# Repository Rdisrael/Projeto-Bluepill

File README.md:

# PCB SHIELD BLUEPILL

# Resumo
Projeto idealizado com o objetivo de auxiliar as aulas de microcontroladores do IFSP-GRU. Por meio da integração de diversos módulos, componentes e protocolos de comunicação em apenas uma placa de circuito impresso, será possível um aprendizado mais rápido e gradual para os alunos.

# Documentação
https://docs.google.com/spreadsheets/d/1qsbzq-tmwSNhySCmtm99sBOb9c8ssFgKAU8AfdciUCU/edit?usp=sharing

*Salve o projeto no disco local(C:) para que todos os componentes e modelos 3D sejam automaticante carregados*

# Autores

**Rogério Dantas**

https://www.linkedin.com/in/roger-dantas-b04025137/

**Israel R. Dutra**

www.linkedin.com/in/israel-rodrigues-dutra-6947281a0

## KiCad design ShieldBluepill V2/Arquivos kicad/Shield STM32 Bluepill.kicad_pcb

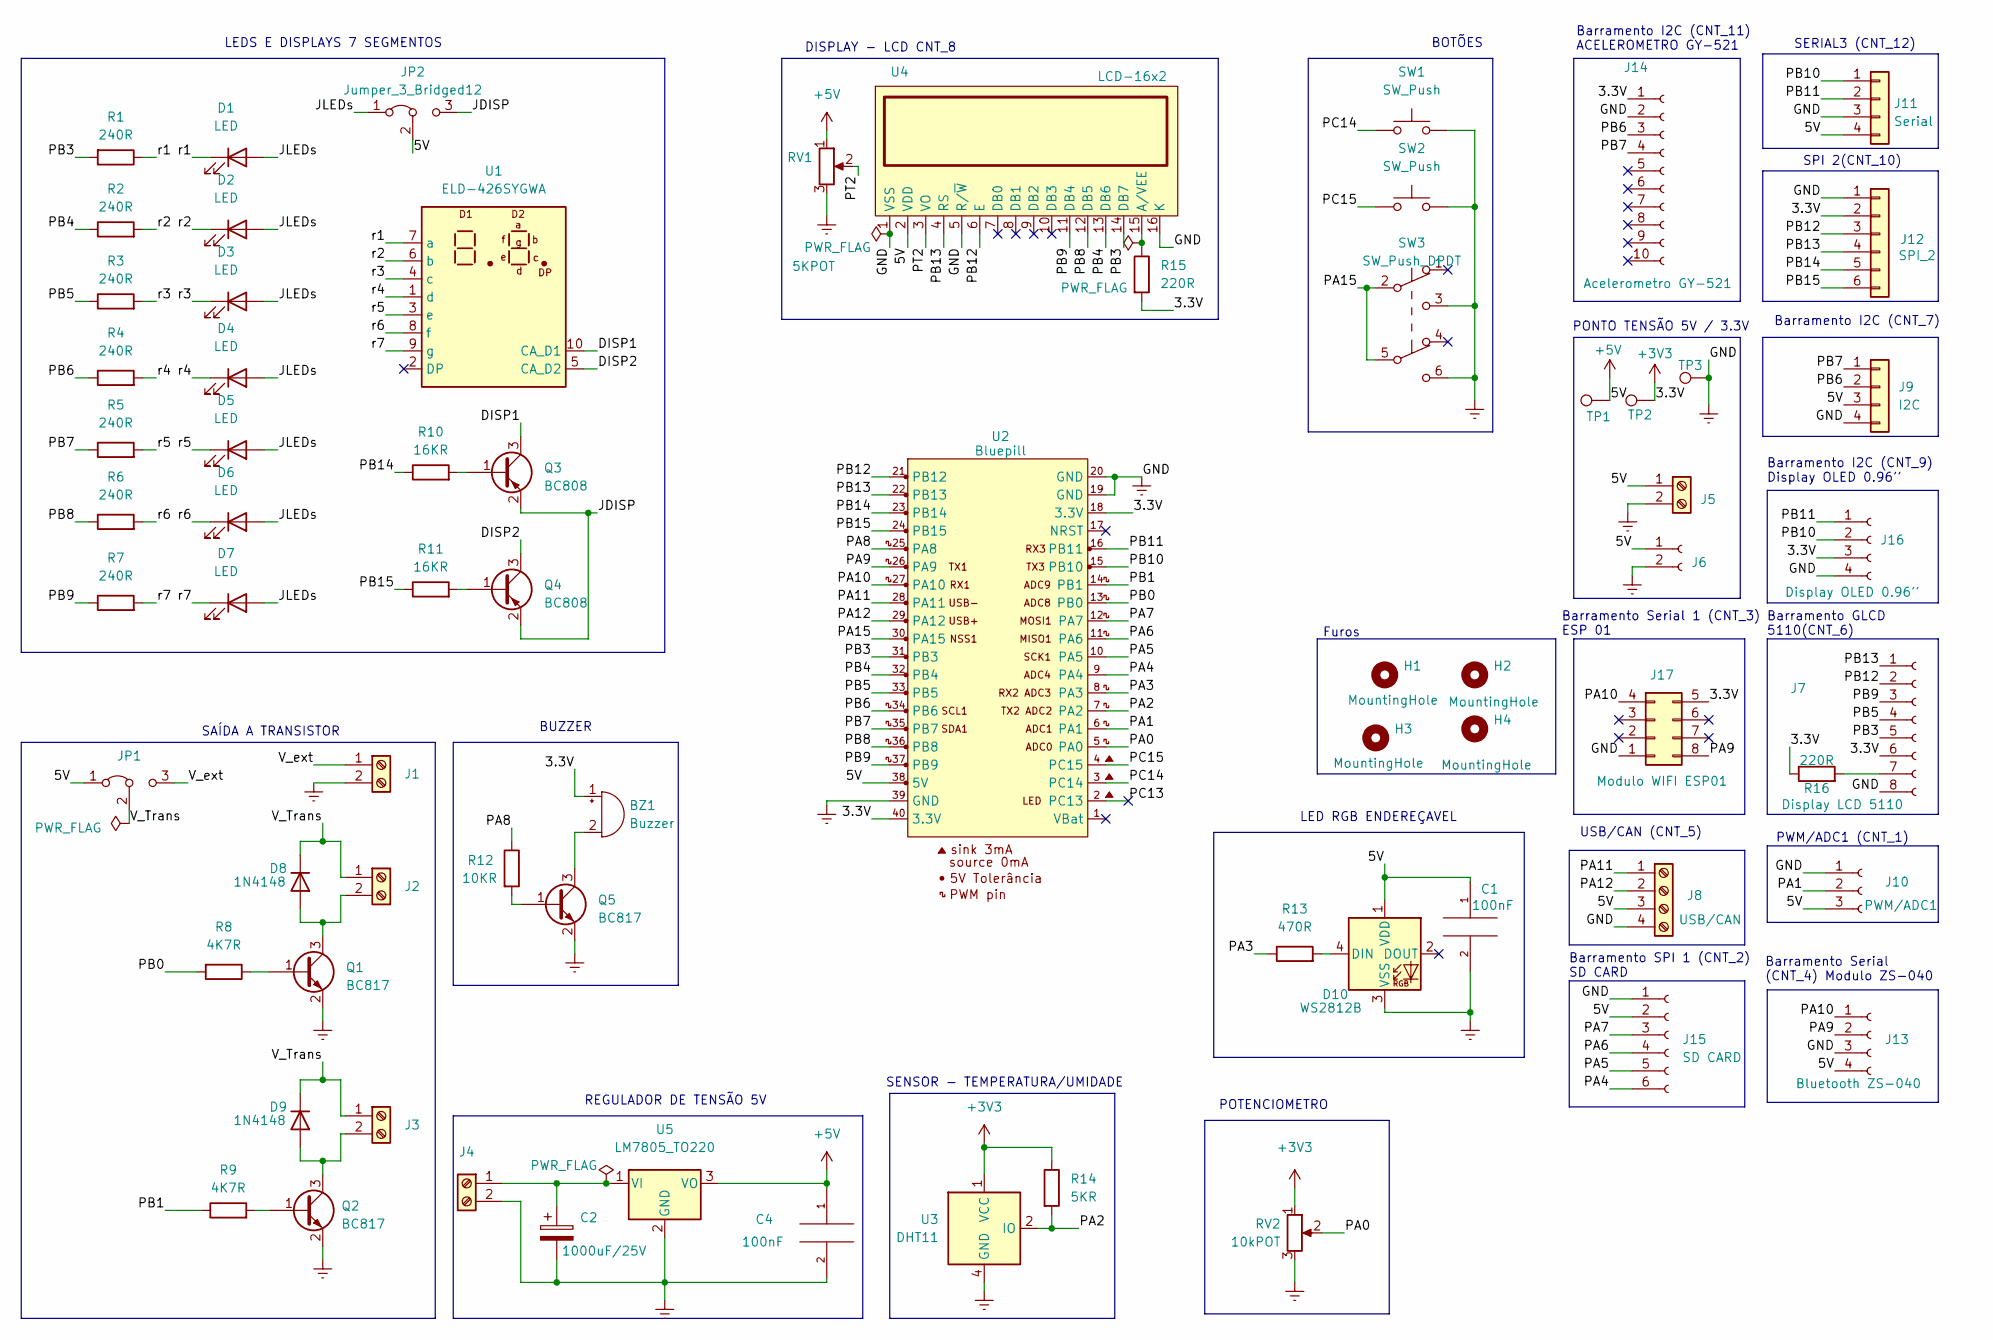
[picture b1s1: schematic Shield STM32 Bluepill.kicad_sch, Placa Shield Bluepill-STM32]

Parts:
BZ1: Buzzer; Buzzer_12x9.5RM7.6
C1, C4: 100nF; C_1206_3216Metric
C2: 1000uF/25V; CP_Elec_10x10
D1, D2, D3, D4, D5, D6, D7: LED; LED_1206_3216Metric
D8, D9: 1N4148; D_1206_3216Metric
D10: WS2812B; LED_WS2812B_PLCC4_5.0x5.0mm_P3.2mm
H1, H2, H3, H4: MountingHole; MountingHole_2.2mm_M2_Pad_Via
J1, J2, J3, J4, J5: Screw_Terminal_01x02; TerminalBlock_Phoenix_MKDS-1,5-2-5.08_1x02_P5.08mm_Horizont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
J6: Conn_01x02_Female; PinSocket_1x02_P2.54mm_Vertical
J7: Display LCD 5110; PinSocket_1x08_P2.54mm_Vertical
J8: USB/CAN; TerminalBlock_Phoenix_MKDS-1,5-4-5.08_1x04_P5.08mm_Horizont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
J9: I2C; Molex_KK-254_AE-6410-04A_1x04_P2.54mm_Vertical
J10: PWM/ADC1; PinSocket_1x03_P2.54mm_Vertical
J11: Serial; Molex_KK-254_AE-6410-04A_1x04_P2.54mm_Vertical
J12: SPI_2; Molex_KK-254_AE-6410-06A_1x06_P2.54mm_Vertical
J13: Bluetooth ZS-040; PinSocket_1x04_P2.54mm_Vertical
J14: Acelerometro GY-521; PinSocket_1x10_P2.54mm_Vertical
J15: SD CARD; PinSocket_1x06_P2.54mm_Vertical
J16: Display OLED 0.96''; PinSocket_1x04_P2.54mm_Vertical
J17: Modulo WIFI ESP01; PinSocket_2x04_P2.54mm_Vertical
JP1, JP2: Jumper_3_Bridged12; PinHeader_1x03_P2.54mm_Vertical
Q1, Q2, Q5: BC817; SOT-23
Q3, Q4: BC808; SOT-23
R1, R2, R3, R4, R5, R6, R7: 240R; R_1206_3216Metric
R8, R9: 4K7R; R_1206_3216Metric
R10, R11: 16KR; R_1206_3216Metric
R12: 10KR; R_1206_3216Metric
R13: 470R; R_1206_3216Metric
R14: 5KR; R_1206_3216Metric
R15, R16: 220R; R_1206_3216Metric
RV1: 5KPOT; Potentiometer_Bourns_3006P_Horizontal
RV2: 10kPOT; Potentiometer_Bourns_3339P_Vertical
SW1, SW2: SW_Push; SW_PUSH_6mm_H7.3mm
SW3: SW_Push_DPDT; SW_TL2201EEYA
TP1, TP2, TP3: TestPoint; TestPoint_Pad_4.0x4.0mm
U1: ELD-426SYGWA; ELD_426XXXX
U2: Bluepill; YAAJ_BluePill_SWD_1
U3: DHT11; Aosong_DHT11_5.5x12.0_P2.54mm
U4: LCD-16x2; WC1602A
U5: LM7805_TO220; TO-220-3_Vertical

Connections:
+3V3: BZ1.1 (-), J7.6, J12.2, J14.1, J16.3, J17.5, R14.1, R15.2, R16.1, RV2.1, TP2.1, U2.18 (3.3V), U2.40 (3.3V), U3.1 (VCC)
+5V: C1.1, C4.1, D10.1 (VDD), J5.1, J6.1, J8.3, J9.3, J10.3, J11.4, J13.4, J15.2, JP1.1 (A), JP2.2 (C), RV1.1, TP1.1, U2.38 (5V), U4.2 (VDD), U5.3 (VO)
/DISP1: Q3.3 (C), U1.10 (CA_D1)
/DISP2: Q4.3 (C), U1.5 (CA_D2)
/JDISP: JP2.3 (B), Q3.2 (E), Q4.2 (E)
/JLEDs: D1.2 (A), D2.2 (A), D3.2 (A), D4.2 (A), D5.2 (A), D6.2 (A), D7.2 (A), JP2.1 (A)
/PA0: RV2.2, U2.5 (PA0)
/PA1: J10.2, U2.6 (PA1)
/PA2: R14.2, U2.7 (PA2), U3.2 (IO)
/PA3: R13.1, U2.8 (PA3)
/PA4: J15.6, U2.9 (PA4)
/PA5: J15.5, U2.10 (PA5)
/PA6: J15.4, U2.11 (PA6)
/PA7: J15.3, U2.12 (PA7)
/PA8: R12.1, U2.25 (PA8)
/PA9: J13.2, J17.8, U2.26 (PA9)
/PA10: J13.1, J17.4, U2.27 (PA10)
/PA11: J8.1, U2.28 (PA11)
/PA12: J8.2, U2.29 (PA12)
/PA15: SW3.2 (B), SW3.5 (B), U2.30 (PA15)
/PB0: R8.2, U2.13 (PB0)
/PB1: R9.1, U2.14 (PB1)
/PB3: J7.5, R1.2, U2.31 (PB3), U4.14 (DB7)
/PB4: R2.1, U2.32 (PB4), U4.13 (DB6)
/PB5: J7.4, R3.1, U2.33 (PB5)
/PB6: J9.2, J14.3, R4.1, U2.34 (PB6)
/PB7: J9.1, J14.4, R5.1, U2.35 (PB7)
/PB8: R6.1, U2.36 (PB8), U4.12 (DB5)
/PB9: J7.3, R7.1, U2.37 (PB9), U4.11 (DB4)
/PB10: J11.1, J16.2, U2.15 (PB10)
/PB11: J11.2, J16.1, U2.16 (PB11)
/PB12: J7.2, J12.3, U2.21 (PB12), U4.6 (E)
/PB13: J7.1, J12.4, U2.22 (PB13), U4.4 (RS)
/PB14: J12.5, R10.1, U2.23 (PB14)
/PB15: J12.6, R11.1, U2.24 (PB15)
/PC13: U2.2 (PC13)
/PC14: SW1.1, U2.3 (PC14)
/PC15: SW2.1, U2.4 (PC15)
/PT2: RV1.2, U4.3 (VO)
/V_Trans: D8.1 (K), D9.1 (K), J2.1, J3.1, JP1.2 (C)
/V_ext: J1.1, JP1.3 (B)
/r1: D1.1 (K), R1.1, U1.7 (a)
/r2: D2.1 (K), R2.2, U1.6 (b)
/r3: D3.1 (K), R3.2, U1.4 (c)
/r4: D4.1 (K), R4.2, U1.1 (d)
/r5: D5.1 (K), R5.2, U1.3 (e)
/r6: D6.1 (K), R6.2, U1.8 (f)
/r7: D7.1 (K), R7.2, U1.9 (g)
Earth: C1.2, C2.2, C4.2, D10.3 (VSS), H1.1, H2.1, H3.1, H4.1, J1.2, J4.2, J5.2, J6.2, J7.8, J8.4, J9.4, J10.1, J11.3, J12.1, J13.3, J14.2, J15.1, J16.4, J17.1, Q1.2 (E), Q2.2 (E), Q5.2 (E), RV1.3, RV2.3, SW1.2, SW2.2, SW3.3 (C), SW3.6 (C), TP3.1, U2.19 (GND), U2.20 (GND), U2.39 (GND), U3.4 (GND), U4.1 (VSS), U4.5 (R/~W), U4.16 (K), U5.2 (GND)
unnamed: BZ1.2 (+), Q5.3 (C)
unnamed: D8.2 (A), J2.2, Q1.3 (C)
unnamed: D9.2 (A), J3.2, Q2.3 (C)
unnamed: D10.4 (DIN), R13.2
unnamed: C2.1, J4.1, U5.1 (VI)
unnamed: J7.7, R16.2
unnamed: Q1.1 (B), R8.1
unnamed: Q2.1 (B), R9.2
unnamed: Q3.1 (B), R10.2
unnamed: Q4.1 (B), R11.2
unnamed: Q5.1 (B), R12.2
unnamed: R15.1, U4.15 (A/VEE)

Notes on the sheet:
SAÍDA A TRANSISTOR
DISPLAY - LCD CNT_8
SENSOR - TEMPERATURA/UMIDADE
LEDS E DISPLAYS 7 SEGMENTOS
REGULADOR DE TENSÃO 5V
Barramento Serial (CNT_4) Modulo ZS-040
Barramento GLCD 5110(CNT_6)
BUZZER
POTENCIOMETRO
PWM/ADC1 (CNT_1)
SERIAL3 (CNT_12)
Furos
Barramento I2C (CNT_9) Display OLED 0.96''
SPI 2(CNT_10)
Barramento Serial 1 (CNT_3) ESP 01
Barramento SPI 1 (CNT_2) SD CARD
Barramento I2C (CNT_11) ACELEROMETRO GY-521
Barramento I2C (CNT_7)
LED RGB ENDEREÇAVEL
USB/CAN (CNT_5)
BOTÕES
PONTO TENSÃO 5V / 3.3V

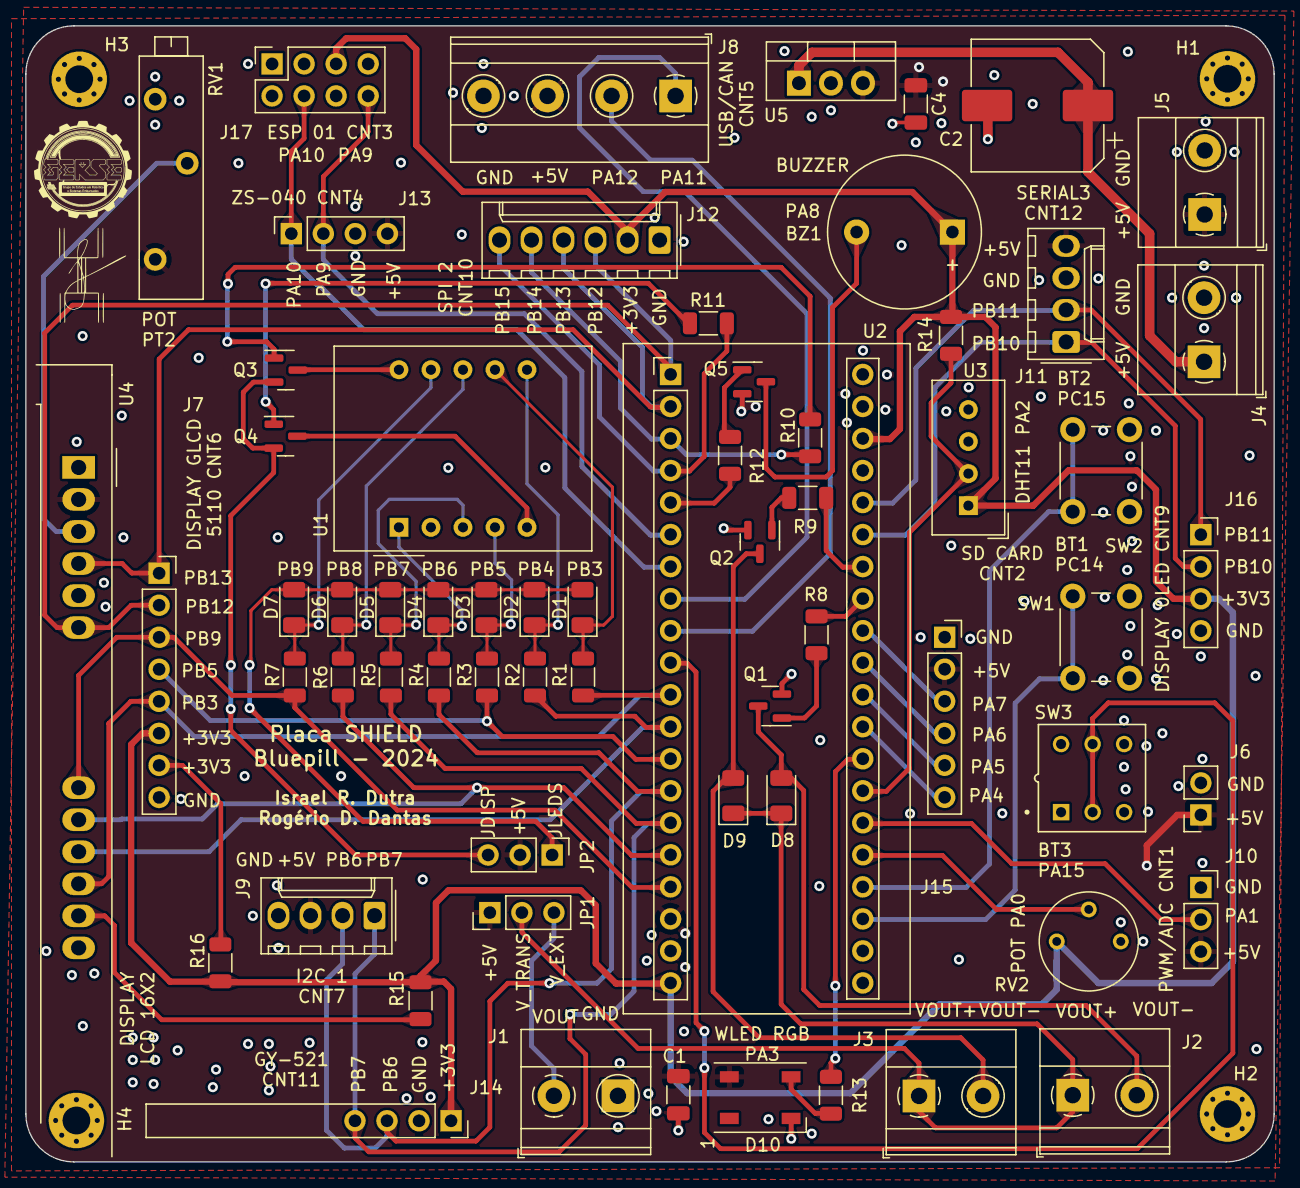
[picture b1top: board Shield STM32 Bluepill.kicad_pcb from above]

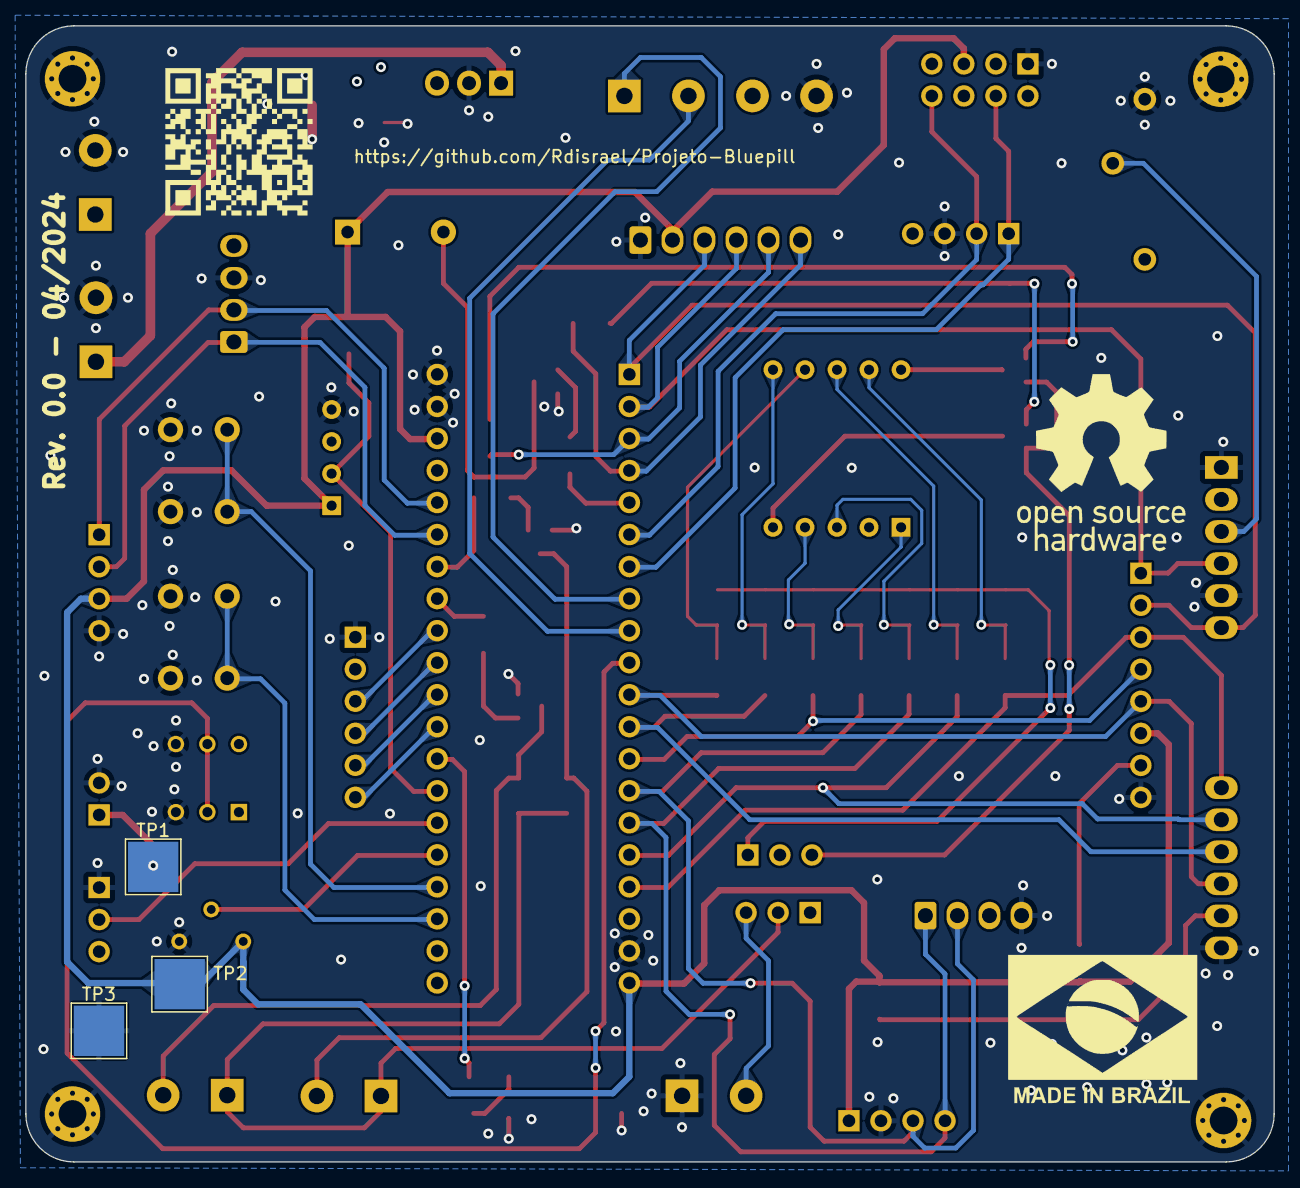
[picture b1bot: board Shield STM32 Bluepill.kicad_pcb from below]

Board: 2 copper layers, 99.0 x 90.1 mm, 71 parts (3 on the bottom side), 60 nets.

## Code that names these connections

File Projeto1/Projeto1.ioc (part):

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Mcu.Name=STM32F103C(8-B)Tx
Mcu.Package=LQFP48
Mcu.UserName=STM32F103C8Tx
PA0-WKUP.GPIOParameters=GPIO_Label
PA0-WKUP.GPIO_Label=POT
PA0-WKUP.Signal=ADCx_IN0
PA13.Mode=Serial_Wire
PA13.Signal=SYS_JTMS-SWDIO
PA14.Mode=Serial_Wire
PA14.Signal=SYS_JTCK-SWCLK
PA15.GPIOParameters=GPIO_Label
PA15.GPIO_Label=SW3
PA15.Signal=GPIO_Input
PA4.GPIOParameters=PinState,GPIO_PuPd
PA4.GPIO_PuPd=GPIO_NOPULL
PA4.PinState=GPIO_PIN_SET
PA4.Signal=GPIO_Output
PA5.Mode=Full_Duplex_Master
PA5.Signal=SPI1_SCK
PA6.Mode=Full_Duplex_Master
PA6.Signal=SPI1_MISO
PA7.Mode=Full_Duplex_Master
PA7.Signal=SPI1_MOSI
PA8.GPIOParameters=GPIO_Label
PA8.GPIO_Label=BUZZER
PA8.Signal=S_TIM1_CH1
PA9.Signal=GPIO_Output
PB10.Mode=I2C
PB10.Signal=I2C2_SCL
PB11.Mode=I2C
PB11.Signal=I2C2_SDA
PB3.GPIOParameters=GPIO_Label
PB3.GPIO_Label=LED1
PB3.Signal=GPIO_Output
PB4.GPIOParameters=GPIO_Label
PB4.GPIO_Label=LED2
PB4.Signal=GPIO_Output
PB5.GPIOParameters=GPIO_Label
PB5.GPIO_Label=LED3
PB5.Signal=GPIO_Output
PB6.GPIOParameters=GPIO_Label
PB6.GPIO_Label=LED4
PB6.Signal=GPIO_Output
PB7.GPIOParameters=GPIO_Label
PB7.GPIO_Label=LED5
PB7.Signal=GPIO_Output
PB8.GPIOParameters=GPIO_Label
PB8.GPIO_Label=LED6
PB8.Signal=GPIO_Output
PB9.GPIOParameters=GPIO_Label
PB9.GPIO_Label=LED7
PB9.Signal=GPIO_Output
PC13-TAMPER-RTC.GPIOParameters=GPIO_Label
PC13-TAMPER-RTC.GPIO_Label=BOARD LED
PC13-TAMPER-RTC.Signal=GPIO_Output
PC14-OSC32_IN.GPIOParameters=GPIO_Label
PC14-OSC32_IN.GPIO_Label=SW1
PC14-OSC32_IN.Signal=GPIO_Input
PC15-OSC32_OUT.GPIOParameters=GPIO_Label
PC15-OSC32_OUT.GPIO_Label=SW2
PC15-OSC32_OUT.Signal=GPIO_Input
PD0-OSC_IN.Mode=HSE-External-Oscillator
PD0-OSC_IN.Signal=RCC_OSC_IN
PD1-OSC_OUT.Mode=HSE-External-Oscillator
PD1-OSC_OUT.Signal=RCC_OSC_OUT
RCC.SYSCLKFreq_VALUE=72000000
RCC.SYSCLKSource=RCC_SYSCLKSOURCE_PLLCLK
board=custom

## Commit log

2024-04-01 Segunda versão Shield Bluepill
2024-04-12 README.md
2024-04-14 REV 0.0
2024-07-01 Programação Inicial
2025-08-14 projeto 1 parte 1
2025-09-05 Projeto 1 parte 2
